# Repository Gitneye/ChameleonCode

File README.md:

# METR2800 Chameleon

Chameleon ftw

## Table of Contents

- [Installation](#installation)
- [Usage](#usage)

## Installation

Instructions on how to install and get the project running.

## Usage

Instructions on how to use the project or its features.

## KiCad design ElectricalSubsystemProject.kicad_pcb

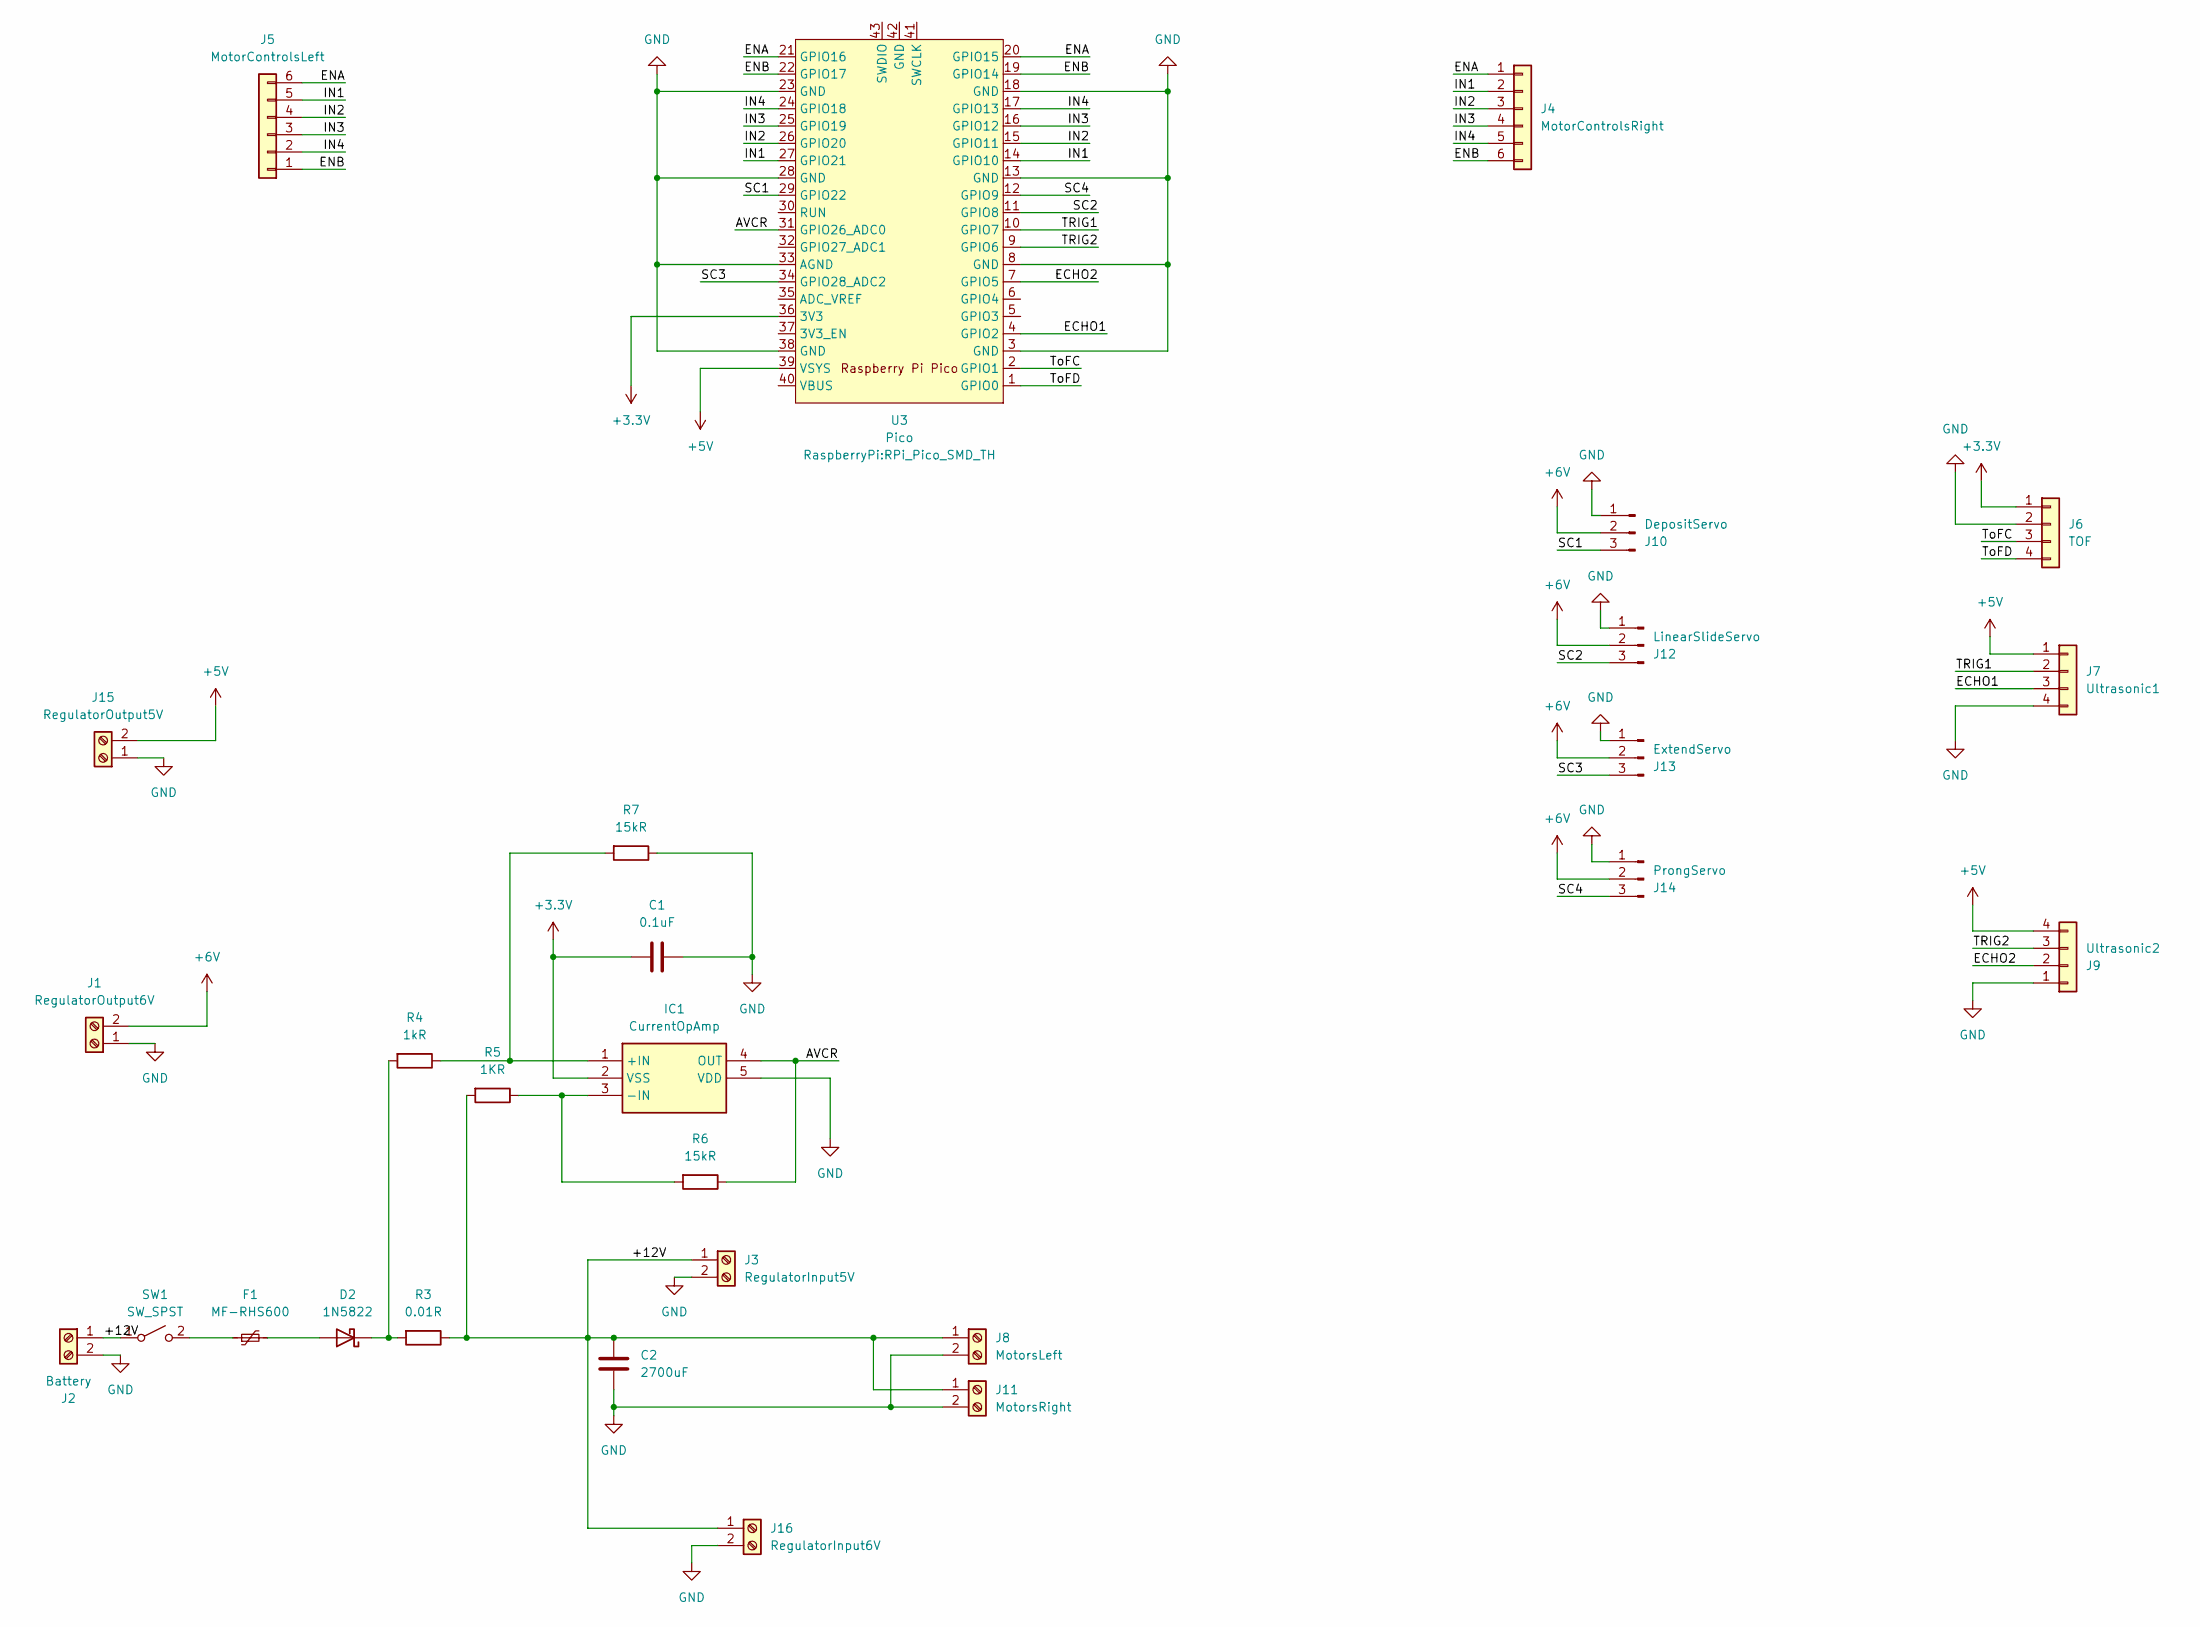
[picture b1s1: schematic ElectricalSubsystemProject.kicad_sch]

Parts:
C1: 0.1uF; CAPPM7343X310N
C2: 2700uF; CP_Radial_D16.0mm_P7.50mm
D2: 1N5822; D_DO-201AD_P15.24mm_Horizontal
F1: MF-RHS600; MFRHS6000
IC1: CurrentOpAmp; SOT95P280X125-5N; Mouser Part Number 755-LMR1802G-LBTR
J1: RegulatorOutput6V; TerminalBlock-P5.0mm-W1.3mm
J2: Battery; TerminalBlock-P5.0mm-W1.3mm
J3: RegulatorInput5V; TerminalBlock-P5.0mm-W1.3mm
J4: MotorControlsRight; PinHeader_1x06_P2.54mm_Vertical
J5: MotorControlsLeft; PinHeader_1x06_P2.54mm_Vertical
J6: TOF; PinHeader_1x04_P2.54mm_Vertical
J7: Ultrasonic1; PinHeader_1x04_P2.54mm_Vertical
J8: MotorsLeft; TerminalBlock-P5.0mm-W1.3mm
J9: Ultrasonic2; PinHeader_1x04_P2.54mm_Vertical
J10: DepositServo; PinHeader_1x03_P2.54mm_Vertical
J11: MotorsRight; TerminalBlock-P5.0mm-W1.3mm
J12: LinearSlideServo; PinHeader_1x03_P2.54mm_Vertical
J13: ExtendServo; PinHeader_1x03_P2.54mm_Vertical
J14: ProngServo; PinHeader_1x03_P2.54mm_Vertical
J15: RegulatorOutput5V; TerminalBlock-P5.0mm-W1.3mm
J16: RegulatorInput6V; TerminalBlock-P5.0mm-W1.3mm
R3: 0.01R; R_2512_6332Metric_Pad1.40x3.35mm_HandSolder
R4: 1kR; R_Axial_DIN0414_L11.9mm_D4.5mm_P5.08mm_Vertical
R5: 1KR; R_Axial_DIN0414_L11.9mm_D4.5mm_P5.08mm_Vertical
R6, R7: 15kR; R_Axial_DIN0414_L11.9mm_D4.5mm_P5.08mm_Vertical
SW1: SW_SPST; SPST_D0.9_P2.5
U3: Pico; RPi_Pico_SMD_TH

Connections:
+3.3V: C1.1, IC1.2 (VSS), J6.1, U3.36 (3V3)
+5V: J7.1, J9.4, J15.2, U3.39 (VSYS)
+6V: J1.2, J10.2, J12.2, J13.2, J14.2
/+12V: C2.1, J2.1, J3.1, J8.1, J11.1, J16.1, R3.1, R5.2, SW1.1 (A)
/AVCR: IC1.4 (OUT), R6.1, U3.31 (GPIO26_ADC0)
/ECHO1: J7.3, U3.4 (GPIO2)
/ECHO2: J9.2, U3.7 (GPIO5)
/ENA: J4.1, J5.6, U3.20 (GPIO15), U3.21 (GPIO16)
/ENB: J4.6, J5.1, U3.19 (GPIO14), U3.22 (GPIO17)
/IN1: J4.2, J5.5, U3.14 (GPIO10), U3.27 (GPIO21)
/IN2: J4.3, J5.4, U3.15 (GPIO11), U3.26 (GPIO20)
/IN3: J4.4, J5.3, U3.16 (GPIO12), U3.25 (GPIO19)
/IN4: J4.5, J5.2, U3.17 (GPIO13), U3.24 (GPIO18)
/SC1: J10.3, U3.29 (GPIO22)
/SC2: J12.3, U3.11 (GPIO8)
/SC3: J13.3, U3.34 (GPIO28_ADC2)
/SC4: J14.3, U3.12 (GPIO9)
/TRIG1: J7.2, U3.10 (GPIO7)
/TRIG2: J9.3, U3.9 (GPIO6)
/ToFC: J6.3, U3.2 (GPIO1)
/ToFD: J6.4, U3.1 (GPIO0)
GND: C1.2, C2.2, IC1.5 (VDD), J1.1, J2.2, J3.2, J6.2, J7.4, J8.2, J9.1, J10.1, J11.2, J12.1, J13.1, J14.1, J15.1, J16.2, R7.1, U3.3 (GND), U3.8 (GND), U3.13 (GND), U3.18 (GND), U3.23 (GND), U3.28 (GND), U3.33 (AGND), U3.38 (GND)
unnamed: D2.2 (A), F1.2
unnamed: D2.1 (K), R3.2, R4.2
unnamed: IC1.1 (+IN), R4.1, R7.2
unnamed: IC1.3 (-IN), R5.1, R6.2
unnamed: F1.1, SW1.2 (B)

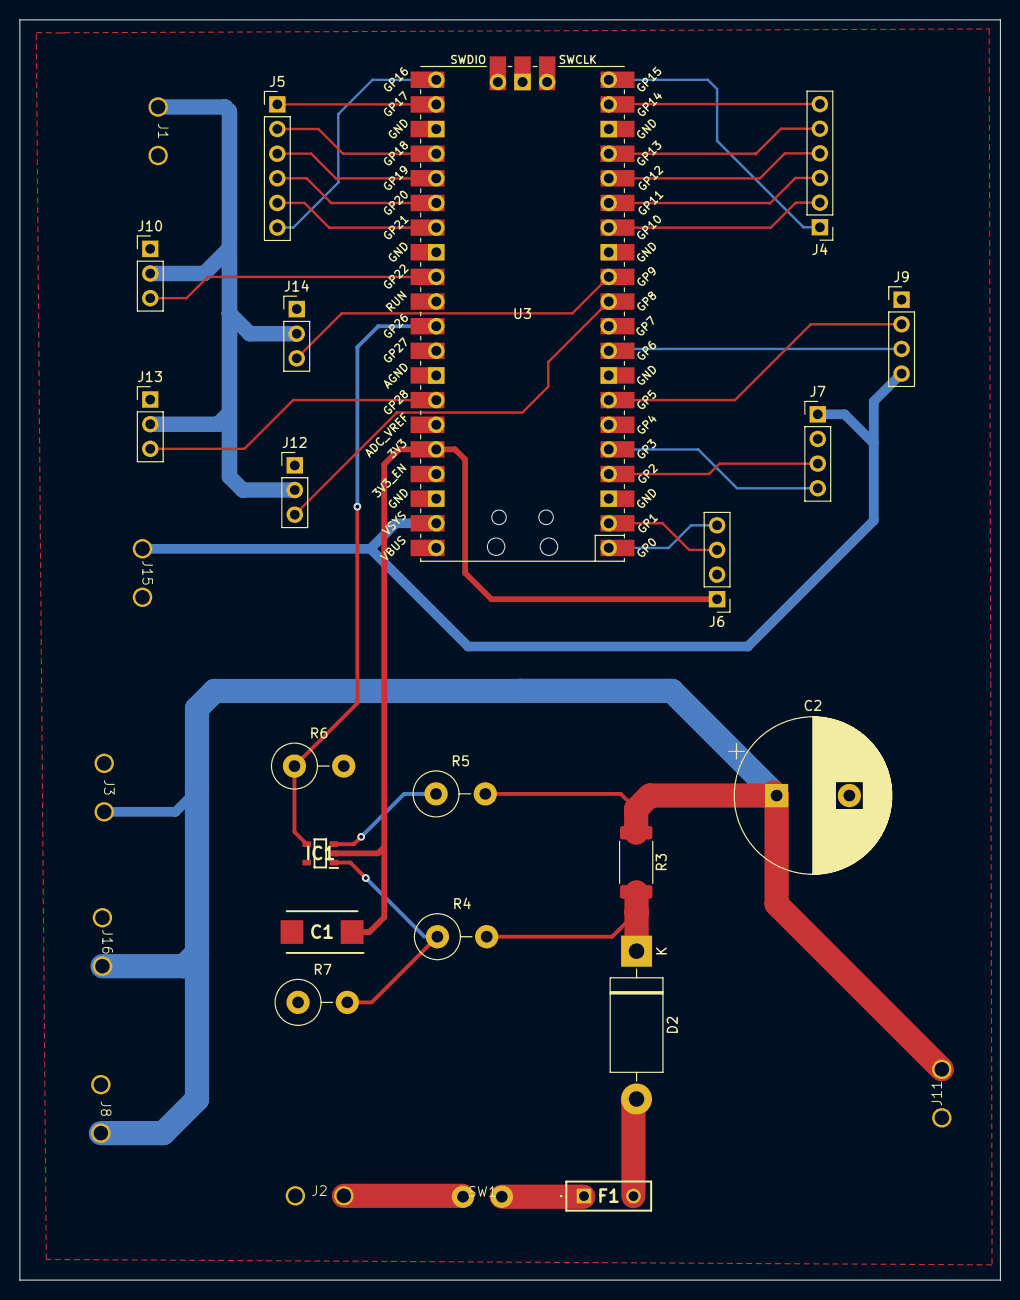
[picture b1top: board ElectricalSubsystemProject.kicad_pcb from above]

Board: 2 copper layers, 101.1 x 129.9 mm, 28 parts (0 on the bottom side), 27 nets.

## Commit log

2024-03-16 Added README.md
2024-04-30 Test KiCad Files
